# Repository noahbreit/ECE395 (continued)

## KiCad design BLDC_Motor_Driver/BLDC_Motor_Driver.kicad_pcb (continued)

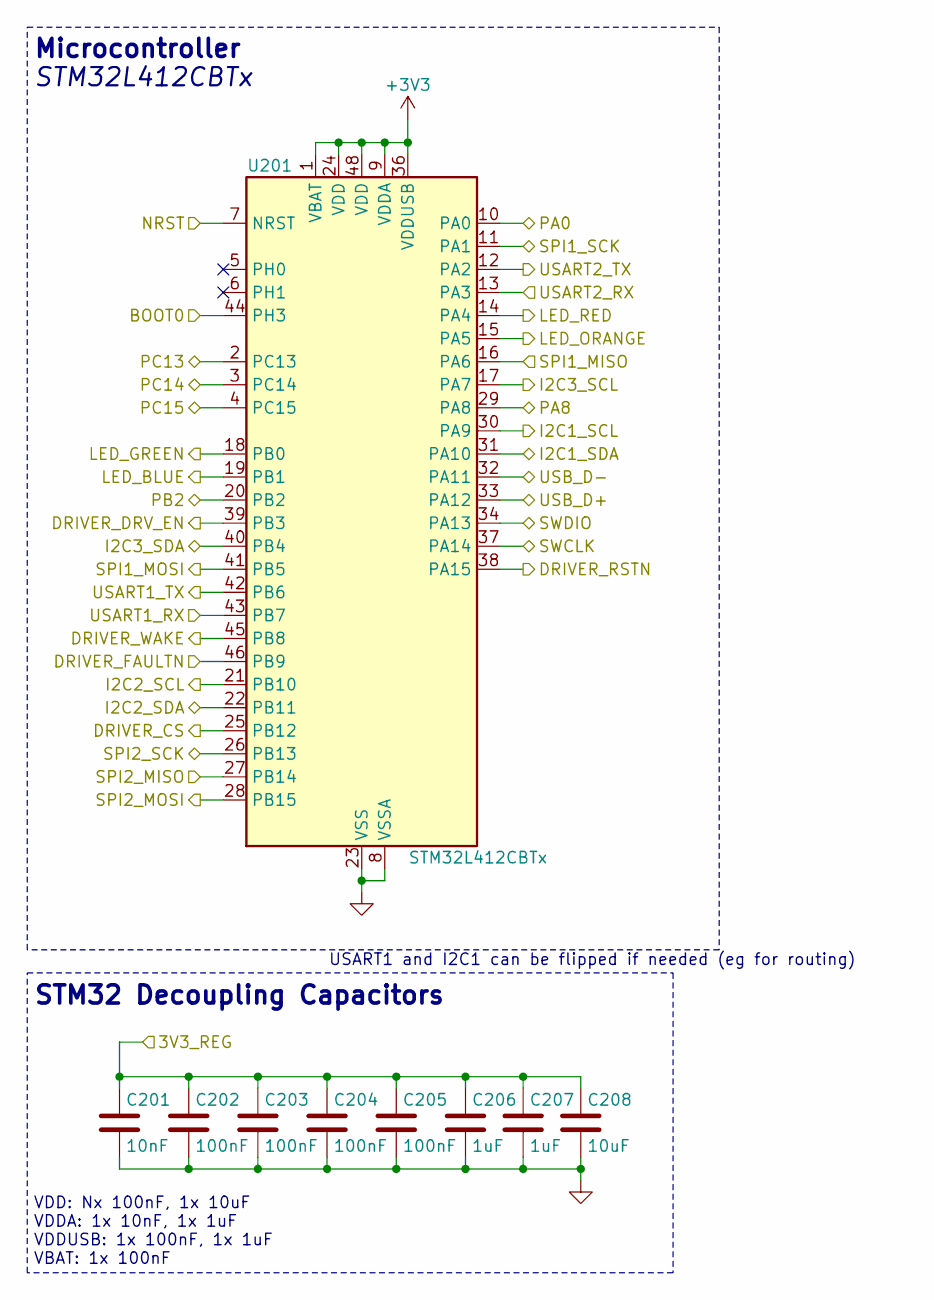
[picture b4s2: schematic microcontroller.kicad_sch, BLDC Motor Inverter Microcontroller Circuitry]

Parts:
C201: 10nF; C_0603_1608Metric
C202, C203, C204, C205: 100nF; C_0603_1608Metric
C206, C207: 1uF; C_0603_1608Metric
C208: 10uF; C_0603_1608Metric
U201: STM32L412CBTx; LQFP-48_7x7mm_P0.5mm

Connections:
+3V3: C201.1, C202.1, C203.1, C204.1, C205.1, C206.1, C207.1, C208.1, U201.1 (VBAT), U201.9 (VDDA), U201.24 (VDD), U201.36 (VDDUSB), U201.48 (VDD); also elsewhere on the board
/BOOT0: U201.44 (PH3); also elsewhere on the board
/DRIVER_CS: U201.25 (PB12); also elsewhere on the board
/DRIVER_DRV_EN: U201.39 (PB3); also elsewhere on the board
/DRIVER_FAULTN: U201.46 (PB9); also elsewhere on the board
/DRIVER_RSTN: U201.38 (PA15); also elsewhere on the board
/DRIVER_WAKE: U201.45 (PB8); also elsewhere on the board
/I2C1_SCL: U201.30 (PA9); also elsewhere on the board
/I2C1_SDA: U201.31 (PA10); also elsewhere on the board
/I2C2_SCL: U201.21 (PB10); also elsewhere on the board
/I2C2_SDA: U201.22 (PB11); also elsewhere on the board
/I2C3_SCL: U201.17 (PA7); also elsewhere on the board
/I2C3_SDA: U201.40 (PB4); also elsewhere on the board
/LED_BLUE: U201.14 (PA4); also elsewhere on the board
/LED_GREEN: U201.15 (PA5); also elsewhere on the board
/LED_ORANGE: U201.18 (PB0); also elsewhere on the board
/LED_RED: U201.19 (PB1); also elsewhere on the board
/NRST: U201.7 (NRST); also elsewhere on the board
/PA0: U201.10 (PA0); also elsewhere on the board
/PA8: U201.29 (PA8); also elsewhere on the board
/PB2: U201.20 (PB2); also elsewhere on the board
/PC13: U201.2 (PC13); also elsewhere on the board
/PC14: U201.3 (PC14); also elsewhere on the board
/PC15: U201.4 (PC15); also elsewhere on the board
/SPI1_MISO: U201.16 (PA6); also elsewhere on the board
/SPI1_MOSI: U201.41 (PB5); also elsewhere on the board
/SPI1_SCK: U201.11 (PA1); also elsewhere on the board
/SPI2_MISO: U201.27 (PB14); also elsewhere on the board
/SPI2_MOSI: U201.28 (PB15); also elsewhere on the board
/SPI2_SCK: U201.26 (PB13); also elsewhere on the board
/SWCLK: U201.34 (PA13); also elsewhere on the board
/SWDIO: U201.37 (PA14); also elsewhere on the board
/USART1_RX: U201.43 (PB7); also elsewhere on the board
/USART1_TX: U201.42 (PB6); also elsewhere on the board
/USART2_RX: U201.13 (PA3); also elsewhere on the board
/USART2_TX: U201.12 (PA2); also elsewhere on the board
/USB_D+: U201.33 (PA12); also elsewhere on the board
/USB_D-: U201.32 (PA11); also elsewhere on the board
GND: C201.2, C202.2, C203.2, C204.2, C205.2, C206.2, C207.2, C208.2, U201.8 (VSSA), U201.23 (VSS), U201.35 (VSS), U201.47 (VSS); also elsewhere on the board

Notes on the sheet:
USART1 and I2C1 can be flipped if needed (eg for routing)
VDD: Nx 100nF, 1x 10uF VDDA: 1x 10nF, 1x 1uF VDDUSB: 1x 100nF, 1x 1uF VBAT: 1x 100nF
STM32 Decoupling Capacitors
STM32L412CBTx
Microcontroller

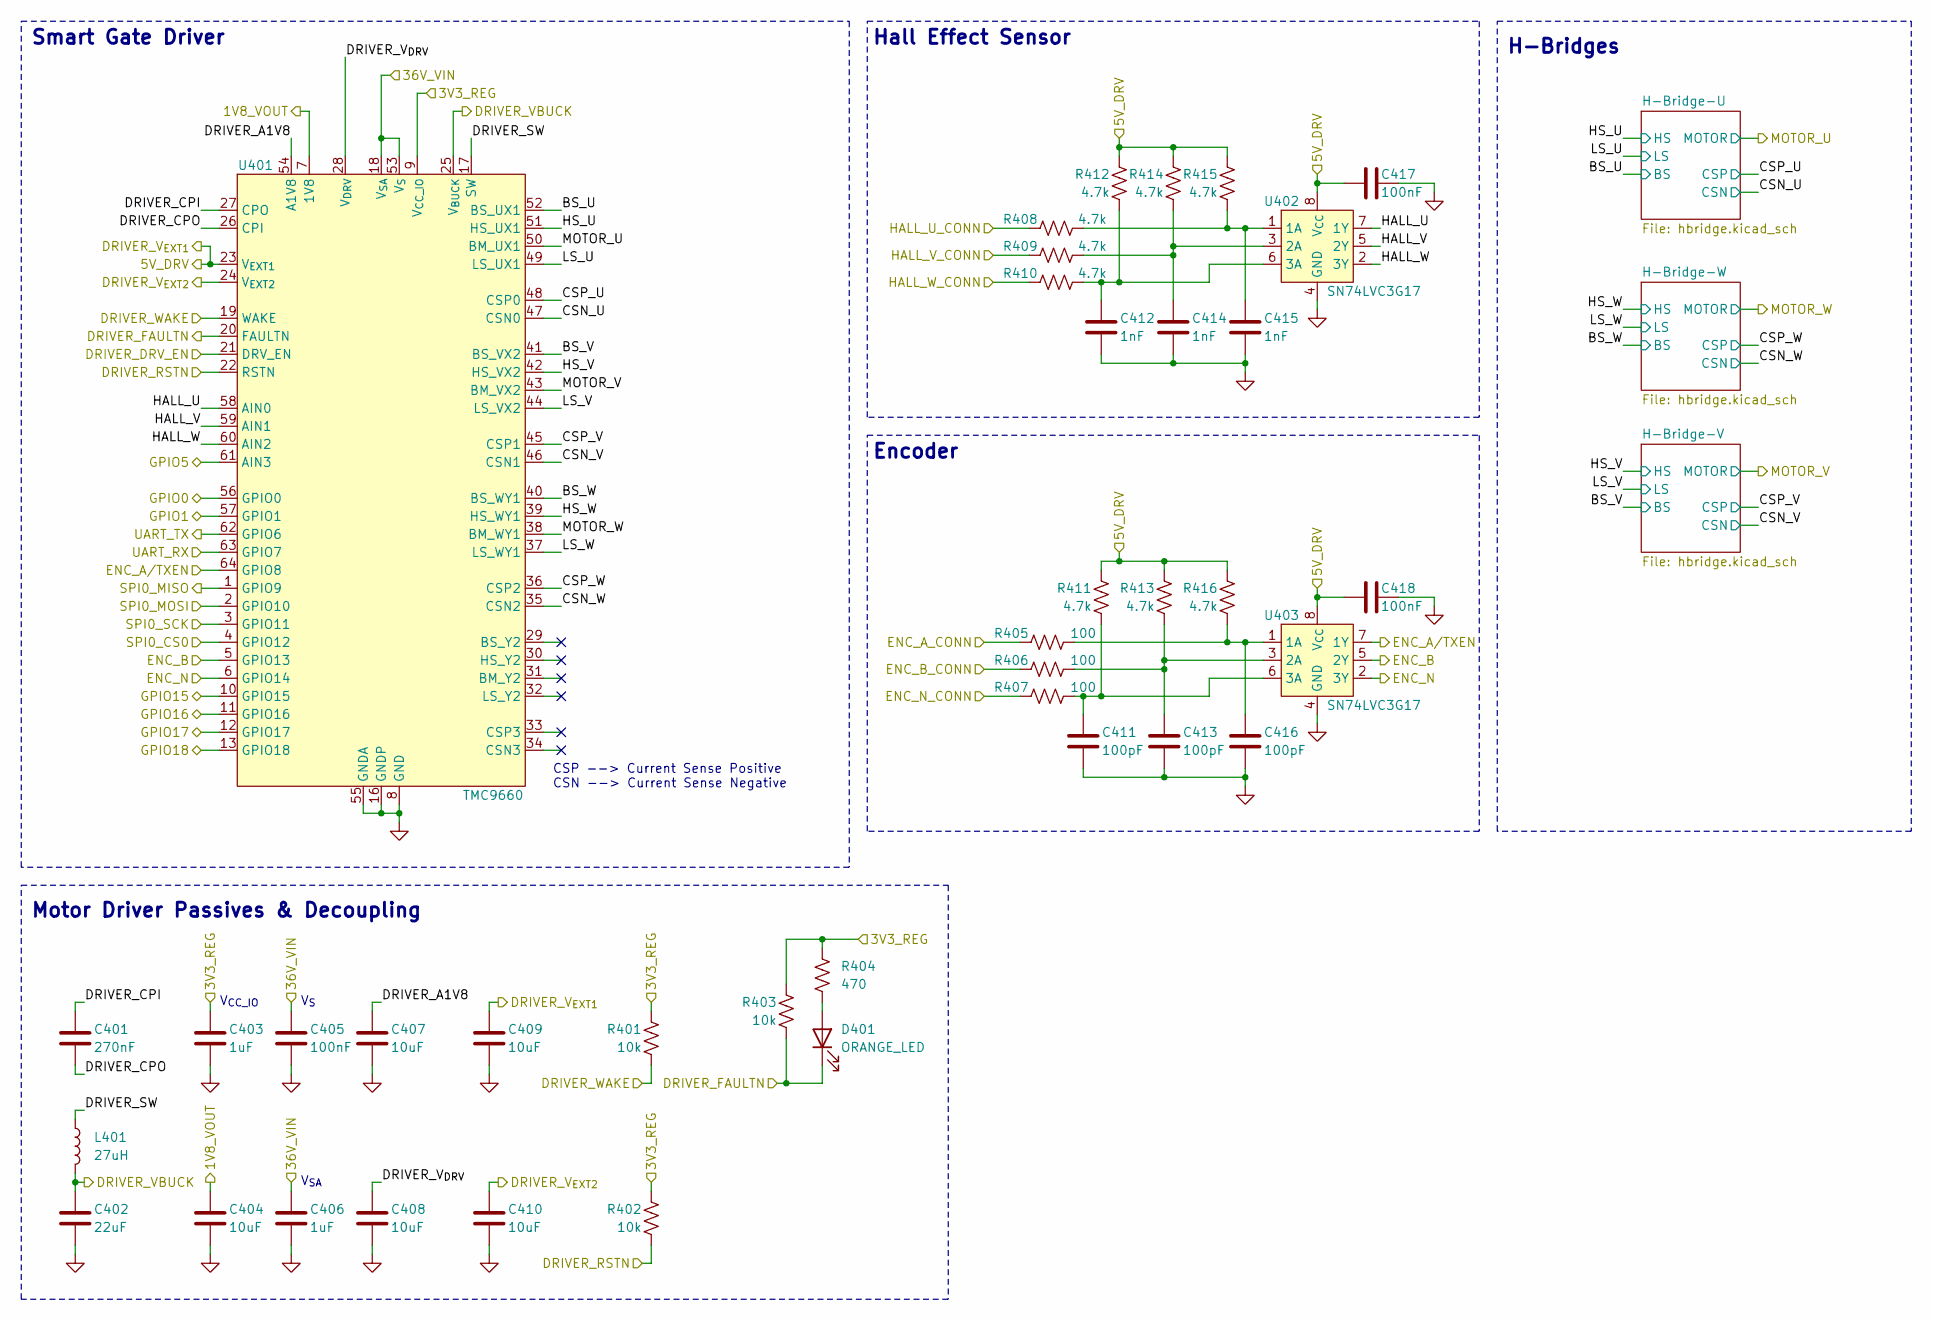
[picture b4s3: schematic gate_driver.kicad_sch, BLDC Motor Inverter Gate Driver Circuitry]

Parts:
C401: 270nF; C_0603_1608Metric
C402: 22uF; C_0805_2012Metric
C403: 1uF; C_0603_1608Metric
C404, C407: 10uF; C_0805_2012Metric
C405: 100nF; C_0805_2012Metric
C406: 1uF; C_1206_3216Metric
C408: 10uF; C_1206_3216Metric
C409, C410: 10uF; C_0603_1608Metric
C411, C413, C416: 100pF; C_0603_1608Metric
C412, C414, C415: 1nF; C_0603_1608Metric
C417, C418: 100nF; C_0603_1608Metric
D401: ORANGE_LED; LED_0603_1608Metric
L401: 27uH; L_APV_ANR6045
R401, R402, R403: 10k; R_0603_1608Metric
R404: 470; R_0603_1608Metric
R405, R406, R407: 100; R_0603_1608Metric
R408, R409, R410, R411, R412, R413, R414, R415, R416: 4.7k; R_0603_1608Metric
U401: TMC9660; QFN-64-1EP_9x9mm_P0.5mm_EP6.3x6.3mm
U402, U403: SN74LVC3G17; VSSOP-8_2.3x2mm_P0.5mm

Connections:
+1V8: C404.1, U401.7 (1V8); also elsewhere on the board
+3V3: C403.1, R401.1, R402.1, R403.1, R404.1, U401.9 (V_{CC_IO}); also elsewhere on the board
+36V: C405.1, C406.1, U401.18 (V_{SA}), U401.53 (V_{S}); also elsewhere on the board
/5V_DRV: C409.1, C417.1, C418.1, R411.1, R412.1, R413.1, R414.1, R415.1, R416.1, U401.23 (V_{EXT1}), U402.8 (V_{CC}), U403.8 (V_{CC}); also elsewhere on the board
/DRIVER_CS: U401.4 (GPIO12); also elsewhere on the board
/DRIVER_DRV_EN: U401.21 (DRV_EN); also elsewhere on the board
/DRIVER_FAULTN: D401.1 (K), R403.2, U401.20 (FAULTN); also elsewhere on the board
/DRIVER_RSTN: R402.2, U401.22 (RSTN); also elsewhere on the board
/DRIVER_V_{BUCK}: C402.1, L401.2, U401.25 (V_{BUCK}); also elsewhere on the board
/DRIVER_V_{EXT2}: C410.1, U401.24 (V_{EXT2}); also elsewhere on the board
/DRIVER_WAKE: R401.2, U401.19 (WAKE); also elsewhere on the board
/ENC_A_CONN: R405.1; also elsewhere on the board
/ENC_B_CONN: R406.1; also elsewhere on the board
/ENC_N_CONN: R407.1; also elsewhere on the board
/Gate-Driver/BS_U: U401.52 (BS_UX1); also elsewhere on the board
/Gate-Driver/BS_V: U401.41 (BS_VX2); also elsewhere on the board
/Gate-Driver/BS_W: U401.40 (BS_WY1); also elsewhere on the board
/Gate-Driver/CSN_U: U401.47 (CSN0); also elsewhere on the board
/Gate-Driver/CSN_V: U401.46 (CSN1); also elsewhere on the board
/Gate-Driver/CSN_W: U401.35 (CSN2); also elsewhere on the board
/Gate-Driver/CSP_U: U401.48 (CSP0); also elsewhere on the board
/Gate-Driver/CSP_V: U401.45 (CSP1); also elsewhere on the board
/Gate-Driver/CSP_W: U401.36 (CSP2); also elsewhere on the board
/Gate-Driver/DRIVER_A1V8: C407.1, U401.54 (A1V8)
/Gate-Driver/DRIVER_CPI: C401.1, U401.27 (CPO)
/Gate-Driver/DRIVER_CPO: C401.2, U401.26 (CPI)
/Gate-Driver/DRIVER_SW: L401.1, U401.17 (SW)
/Gate-Driver/DRIVER_V_{DRV}: C408.1, U401.28 (V_{DRV})
/Gate-Driver/ENC_A/TXEN: U401.64 (GPIO8), U403.7 (1Y); also elsewhere on the board
/Gate-Driver/ENC_B: U401.5 (GPIO13), U403.5 (2Y)
/Gate-Driver/ENC_N: U401.6 (GPIO14), U403.2 (3Y)
/Gate-Driver/GPIO0: U401.56 (GPIO0); also elsewhere on the board
/Gate-Driver/GPIO1: U401.57 (GPIO1); also elsewhere on the board
/Gate-Driver/GPIO5: U401.61 (AIN3); also elsewhere on the board
/Gate-Driver/GPIO15: U401.10 (GPIO15); also elsewhere on the board
/Gate-Driver/GPIO16: U401.11 (GPIO16); also elsewhere on the board
/Gate-Driver/GPIO17: U401.12 (GPIO17); also elsewhere on the board
/Gate-Driver/GPIO18: U401.13 (GPIO18); also elsewhere on the board
/Gate-Driver/HALL_U: U401.58 (AIN0), U402.7 (1Y)
/Gate-Driver/HALL_V: U401.59 (AIN1), U402.5 (2Y)
/Gate-Driver/HALL_W: U401.60 (AIN2), U402.2 (3Y)
/Gate-Driver/HS_U: U401.51 (HS_UX1); also elsewhere on the board
/Gate-Driver/HS_V: U401.42 (HS_VX2); also elsewhere on the board
/Gate-Driver/HS_W: U401.39 (HS_WY1); also elsewhere on the board
/Gate-Driver/LS_U: U401.49 (LS_UX1); also elsewhere on the board
/Gate-Driver/LS_V: U401.44 (LS_VX2); also elsewhere on the board
/Gate-Driver/LS_W: U401.37 (LS_WY1); also elsewhere on the board
/HALL_U_CONN: R408.1; also elsewhere on the board
/HALL_V_CONN: R409.1; also elsewhere on the board
/HALL_W_CONN: R410.1; also elsewhere on the board
/MOTOR_U: U401.50 (BM_UX1); also elsewhere on the board
/MOTOR_V: U401.43 (BM_VX2); also elsewhere on the board
/MOTOR_W: U401.38 (BM_WY1); also elsewhere on the board
/SPI2_MISO: U401.1 (GPIO9); also elsewhere on the board
/SPI2_MOSI: U401.2 (GPIO10); also elsewhere on the board
/SPI2_SCK: U401.3 (GPIO11); also elsewhere on the board
/USART1_RX: U401.62 (GPIO6); also elsewhere on the board
/USART1_TX: U401.63 (GPIO7); also elsewhere on the board
GND: C402.2, C403.2, C404.2, C405.2, C406.2, C407.2, C408.2, C409.2, C410.2, C411.2, C412.2, C413.2, C414.2, C415.2, C416.2, C417.2, C418.2, U401.8 (GND), U401.16 (GNDP), U401.55 (GNDA), U401.65 (EP), U402.4 (GND), U403.4 (GND); also elsewhere on the board
unnamed: D401.2 (A), R404.2
unnamed: C415.1, R408.2, R415.2, U402.1 (1A)
unnamed: C414.1, R409.2, R414.2, U402.3 (2A)
unnamed: C412.1, R410.2, R412.2, U402.6 (3A)
unnamed: C416.1, R405.2, R416.2, U403.1 (1A)
unnamed: C413.1, R406.2, R413.2, U403.3 (2A)
unnamed: C411.1, R407.2, R411.2, U403.6 (3A)

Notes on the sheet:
H-Bridges
V_{S}
Motor Driver Passives & Decoupling
Hall Effect Sensor
V_{CC_IO}
Encoder
Smart Gate Driver
CSP --> Current Sense Positive CSN --> Current Sense Negative
V_{SA}

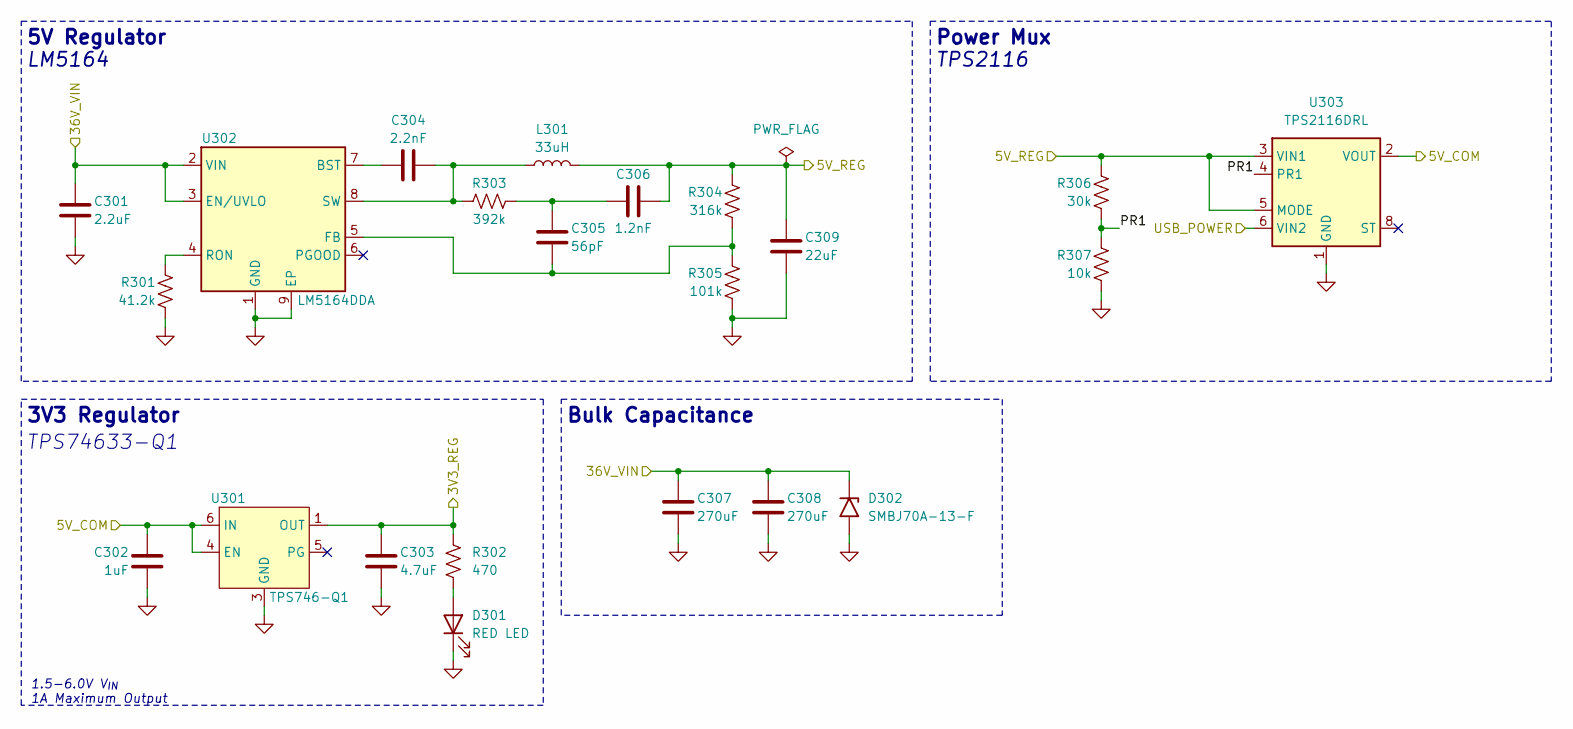
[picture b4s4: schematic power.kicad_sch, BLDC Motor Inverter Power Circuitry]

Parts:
C301: 2.2uF; C_1210_3225Metric
C302: 1uF; C_0603_1608Metric
C303: 4.7uF; C_0603_1608Metric
C304: 2.2nF; C_0805_2012Metric
C305: 56pF; C_0805_2012Metric
C306: 1.2nF; C_0603_1608Metric
C307, C308: 270uF; CP_Radial_D16.0mm_P7.50mm
C309: 22uF; C_1206_3216Metric
D301: RED LED; LED_0603_1608Metric
D302: SMBJ70A-13-F; D_SMB
L301: 33uH; L_Vishay_IHLP-3232
R301: 41.2k; R_0603_1608Metric
R302: 470; R_0603_1608Metric
R303: 392k; R_0603_1608Metric
R304: 316k; R_0603_1608Metric
R305: 101k; R_0603_1608Metric
R306: 30k; R_0603_1608Metric
R307: 10k; R_0603_1608Metric
U301: TPS746-Q1; WSON-6-1EP_2x2mm_P0.65mm_EP1x1.6mm
U302: LM5164DDA; HSOP-8-1EP_3.9x4.9mm_P1.27mm_EP2.41x3.1mm_ThermalVias
U303: TPS2116DRL; SOT-583-8

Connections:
+3V3: C303.1, R302.1, U301.1 (OUT); also elsewhere on the board
+36V: C301.1, C307.1, C308.1, D302.1 (A1), U302.2 (VIN), U302.3 (EN/UVLO); also elsewhere on the board
/5V_COM: C302.1, U301.4 (EN), U301.6 (IN), U303.2 (VOUT), U303.7 (VOUT); also elsewhere on the board
/5V_REG: C306.2, C309.1, L301.2, R304.1, R306.1, U303.3 (VIN1), U303.5 (MODE); also elsewhere on the board
/Power/PR1: R306.2, R307.1, U303.4 (PR1)
/USB_POWER: U303.6 (VIN2); also elsewhere on the board
GND: C301.2, C302.2, C303.2, C307.2, C308.2, C309.2, D301.1 (K), D302.2 (A2), R301.2, R305.2, R307.2, U301.3 (GND), U301.7 (EP), U302.1 (GND), U302.9 (EP), U303.1 (GND); also elsewhere on the board
unnamed: C305.1, C306.1, R303.2
unnamed: D301.2 (A), R302.2
unnamed: C304.1, U302.7 (BST)
unnamed: C305.2, R304.2, R305.1, U302.5 (FB)
unnamed: R301.1, U302.4 (RON)
unnamed: C304.2, L301.1, R303.1, U302.8 (SW)

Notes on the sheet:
5V Regulator
Bulk Capacitance
LM5164
Power Mux
TPS74633-Q1
TPS2116
3V3 Regulator
1.5-6.0V V_{IN} 1A Maximum Output

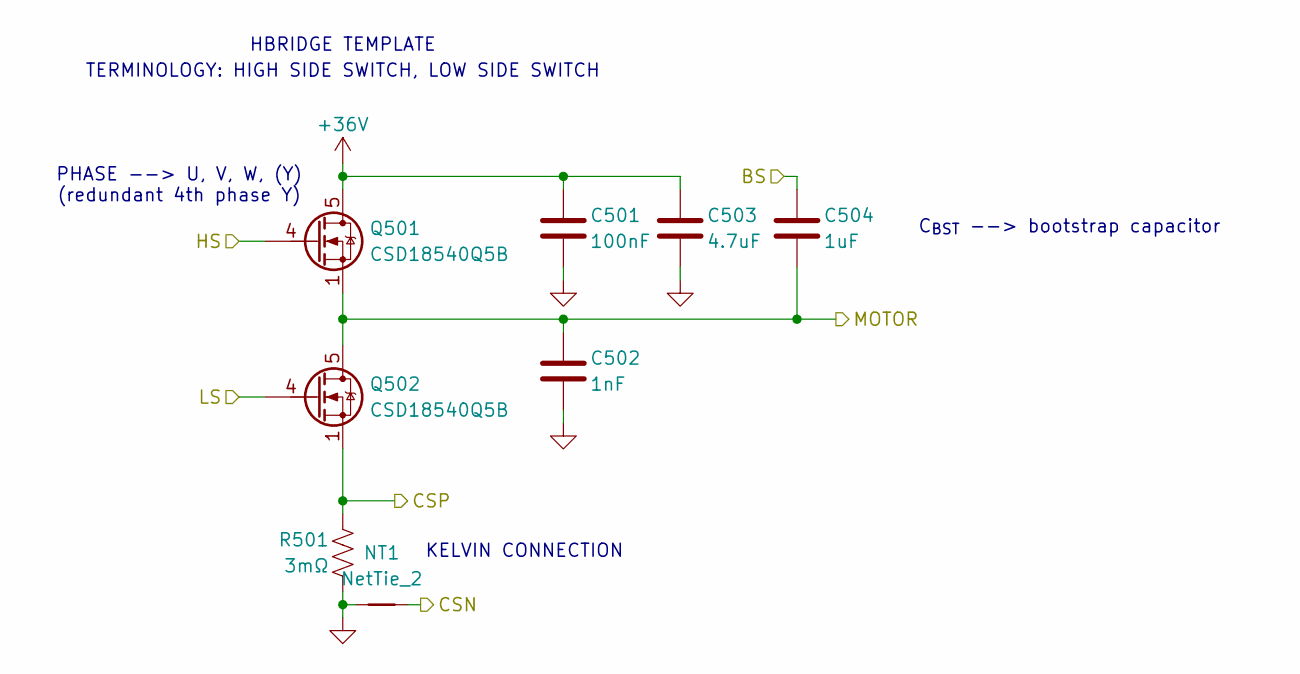
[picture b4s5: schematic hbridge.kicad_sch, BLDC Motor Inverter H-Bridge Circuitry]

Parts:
C501: 100nF; C_0805_2012Metric
C502: 1nF; C_0603_1608Metric
C503: 4.7uF; C_1210_3225Metric
C504: 1uF; C_0603_1608Metric
NT1: NetTie_2; NetTie-2_THT_Pad0.3mm
Q501, Q502: CSD18540Q5B; TDSON-8-1
R501: 3mΩ; R_2512_6332Metric_Pad1.40x3.35mm_HandSolder

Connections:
+36V: C501.1, C503.1, Q501.5 (D); also elsewhere on the board
/Gate-Driver/BS_U: C504.1; also elsewhere on the board
/Gate-Driver/CSN_U: NT1.2; also elsewhere on the board
/Gate-Driver/CSP_U: Q502.1 (S), Q502.2 (S), Q502.3 (S), R501.1; also elsewhere on the board
/Gate-Driver/HS_U: Q501.4 (G); also elsewhere on the board
/Gate-Driver/LS_U: Q502.4 (G); also elsewhere on the board
/MOTOR_U: C502.1, C504.2, Q501.1 (S), Q501.2 (S), Q501.3 (S), Q502.5 (D); also elsewhere on the board
GND: C501.2, C502.2, C503.2, NT1.1, R501.2; also elsewhere on the board

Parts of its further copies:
C601, C701: 100nF; C_0805_2012Metric
C602, C702: 1nF; C_0603_1608Metric
C603, C703: 4.7uF; C_1210_3225Metric
C604, C704: 1uF; C_0603_1608Metric
NT2, NT3: NetTie_2; NetTie-2_THT_Pad0.3mm
Q601, Q602, Q701, Q702: CSD18540Q5B; TDSON-8-1
R601, R701: 3mΩ; R_2512_6332Metric_Pad1.40x3.35mm_HandSolder

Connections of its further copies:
+36V: C601.1, C603.1, C701.1, C703.1, Q601.5 (D), Q701.5 (D); also elsewhere on the board
/Gate-Driver/BS_V: C604.1; also elsewhere on the board
/Gate-Driver/BS_W: C704.1; also elsewhere on the board
/Gate-Driver/CSN_V: NT2.2; also elsewhere on the board
/Gate-Driver/CSN_W: NT3.2; also elsewhere on the board
/Gate-Driver/CSP_V: Q602.1 (S), Q602.2 (S), Q602.3 (S), R601.1; also elsewhere on the board
/Gate-Driver/CSP_W: Q702.1 (S), Q702.2 (S), Q702.3 (S), R701.1; also elsewhere on the board
/Gate-Driver/HS_V: Q601.4 (G); also elsewhere on the board
/Gate-Driver/HS_W: Q701.4 (G); also elsewhere on the board
/Gate-Driver/LS_V: Q602.4 (G); also elsewhere on the board
/Gate-Driver/LS_W: Q702.4 (G); also elsewhere on the board
/MOTOR_V: C602.1, C604.2, Q601.1 (S), Q601.2 (S), Q601.3 (S), Q602.5 (D); also elsewhere on the board
/MOTOR_W: C702.1, C704.2, Q701.1 (S), Q701.2 (S), Q701.3 (S), Q702.5 (D); also elsewhere on the board
GND: C601.2, C602.2, C603.2, C701.2, C702.2, C703.2, NT2.1, NT3.1, R601.2, R701.2; also elsewhere on the board

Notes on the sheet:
TERMINOLOGY: HIGH SIDE SWITCH, LOW SIDE SWITCH
KELVIN CONNECTION
C_{BST} --> bootstrap capacitor
HBRIDGE TEMPLATE
PHASE --> U, V, W, (Y) (redundant 4th phase Y)

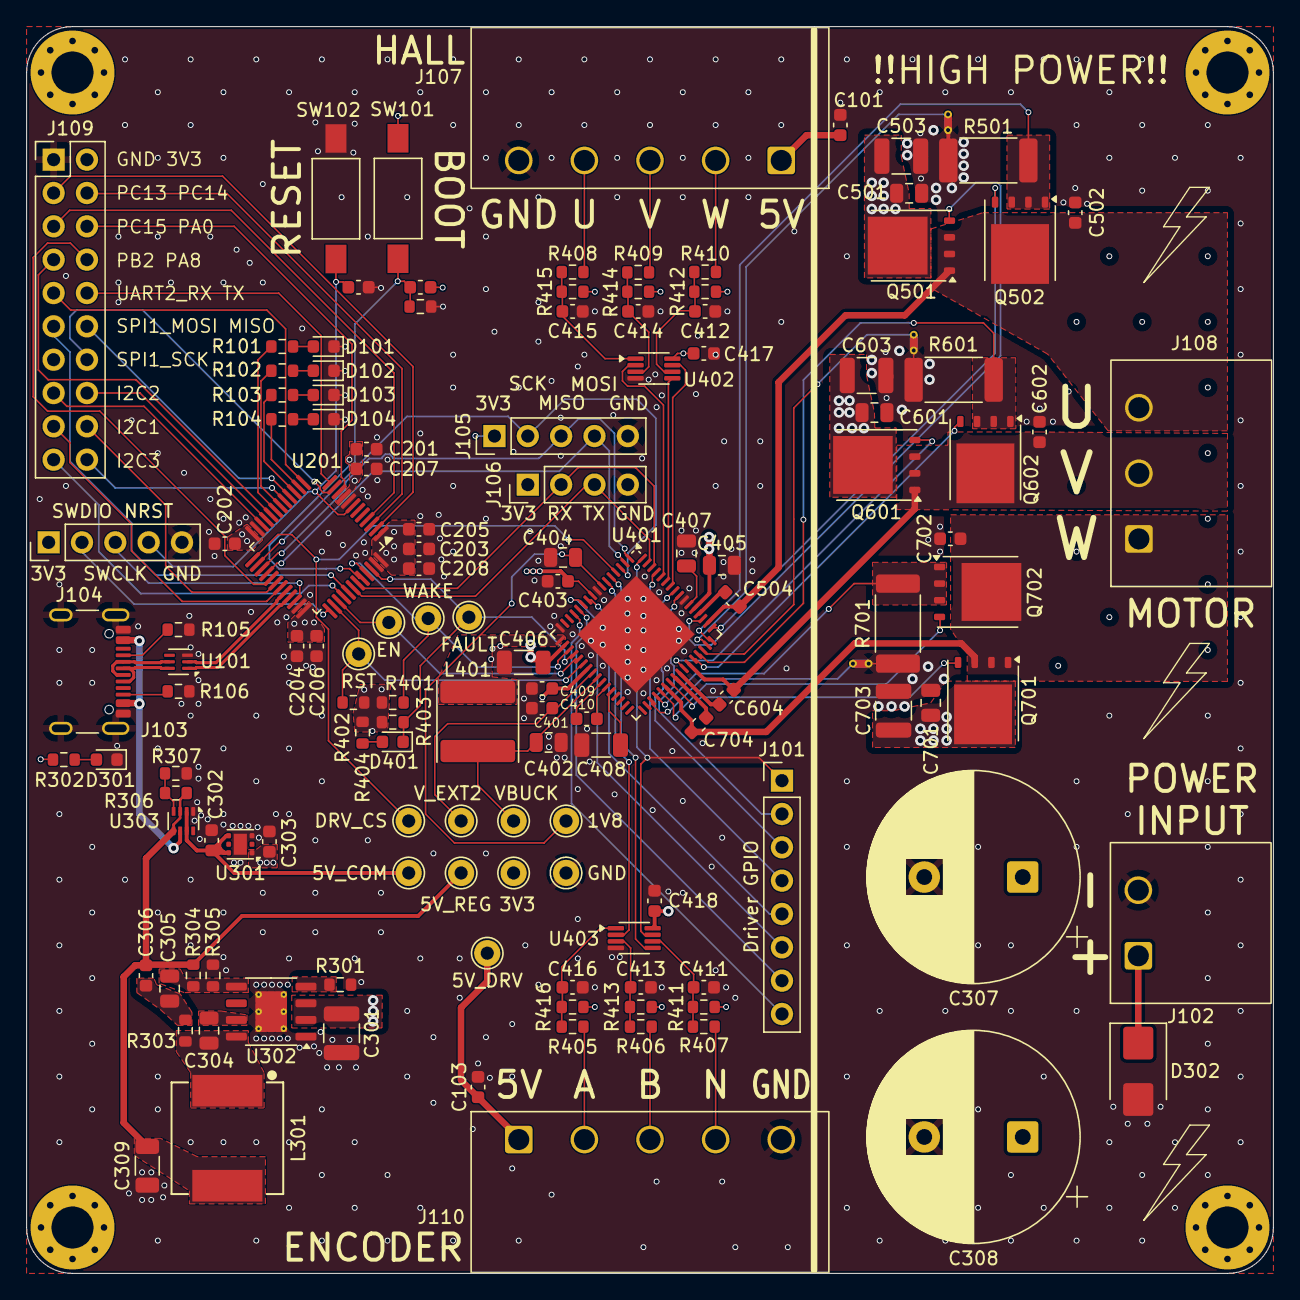
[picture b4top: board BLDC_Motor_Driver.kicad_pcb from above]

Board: 4 copper layers, 95.0 x 95.0 mm, 139 parts (0 on the bottom side), 111 nets.

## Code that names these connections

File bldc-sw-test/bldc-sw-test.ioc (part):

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Mcu.Name=STM32L412CBTx
Mcu.Package=LQFP48
Mcu.UserName=STM32L412CBTx
PA1.Signal=SPI1_SCK
PA10.Signal=I2C1_SDA
PA11.Mode=Device
PA11.Signal=USB_DM
PA12.Mode=Device
PA12.Signal=USB_DP
PA15\ (JTDI).Signal=GPIO_Output
PA2.Signal=USART2_TX
PA3.Signal=USART2_RX
PA4.Signal=GPIO_Output
PA5.Signal=GPIO_Output
PA6.Signal=SPI1_MISO
PA7.Signal=I2C3_SCL
PA9.Signal=I2C1_SCL
PB0.Signal=GPIO_Output
PB1.Signal=GPIO_Output
PB10.Signal=I2C2_SCL
PB11.Signal=I2C2_SDA
PB12.Signal=GPIO_Output
PB13.Signal=SPI2_SCK
PB14.Signal=SPI2_MISO
PB15.Signal=SPI2_MOSI
PB3\ (JTDO/TRACESWO).Signal=GPIO_Output
PB4\ (NJTRST).Signal=I2C3_SDA
PB5.Signal=SPI1_MOSI
PB6.Mode=Asynchronous
PB6.Signal=USART1_TX
PB7.Mode=Asynchronous
PB7.Signal=USART1_RX
PB8.Signal=GPIO_Output
PB9.Signal=GPIO_Input
RCC.HSE_VALUE=8000000
RCC.SYSCLKFreq_VALUE=80000000
RCC.SYSCLKSource=RCC_SYSCLKSOURCE_PLLCLK
board=custom

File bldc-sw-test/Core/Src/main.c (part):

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}

/* * Holds the TMC9660 in hardware reset and waits for a user start command.
 * Note: Uses PA15 (RSTN) and monitors PB9 (FAULTN) per schematic labels.
 */
void tmc9660_app_HoldInResetUntilReady(void) {
    uint8_t user_cmd = 0;
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    // 1. Assert Hardware Reset (Active Low)
    HAL_GPIO_WritePin(GPIOA, GPIO_PIN_15, GPIO_PIN_RESET);

    // 2. Ensure Wake is high (PB8 is DRIVER_WAKE in schematic)
    HAL_GPIO_WritePin(GPIOB, GPIO_PIN_8, GPIO_PIN_SET);

    // 3. Ensure Drive_En is low (PB3)
    HAL_GPIO_WritePin(GPIOB, GPIO_PIN_3, GPIO_PIN_RESET);

    UART_Printf("\r\n[SYSTEM] TMC9660 held in RESET to prevent brownout.\r\n");
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            UserRxBufferFS[0] = 0; // Clear for next use
        }

        // Optional: Monitor Fault pin (PB9) while waiting
        if (HAL_GPIO_ReadPin(GPIOB, GPIO_PIN_9) == GPIO_PIN_RESET) {
            // Add warning if driver indicates a hardware fault during standby
        }
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 */
void tmc9660_app_ReportConditionAndHalt(void) {
    // 1. Assert Safe State (Active Off)
    // DRIVER_DRV_EN (PB3): Setting LOW to disable the gate driver bridge
    HAL_GPIO_WritePin(GPIOB, GPIO_PIN_3, GPIO_PIN_RESET);

    // DRIVER_RSTN (PA15): Pulling LOW to hold the TMC9660 in Hardware Reset
    HAL_GPIO_WritePin(GPIOA, GPIO_PIN_15, GPIO_PIN_RESET);

    // 2. Read Fault Condition
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}

void tmc9660_app_EnableDrive(void) {
	// Set Drive_En is HIGH (PB3)
	HAL_GPIO_WritePin(GPIOB, GPIO_PIN_3, GPIO_PIN_SET);
}

void tmc9660_app_DisableDrive(void) {
	// Set Drive_En is LOW (PB3)
	HAL_GPIO_WritePin(GPIOB, GPIO_PIN_3, GPIO_PIN_RESET);
}

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    }

    // 3. INTERFACE CONFIG
    // UART Enable (Disable=0), SPI Slave Disable(1), TX=GPIO6(0), RX=GPIO7(0), Baud=auto16(7), SCK=GPIO11(1)
    blStatus = tmc9660_bl_sendCommand(tmc9660_id, TMC9660_BLCMD_SET_ADDRESS, CONFIG_BOOT_03_BOOT_INTERFACE, &rVal);
    if (blStatus != TMC9660_BLSTATUS_OK) {
  	  ERR_Handler(__LINE__);
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    }
    reg = field_update16(reg, CONFIG_BOOT_03_INTERFACE_BL_DISABLE_UART_FIELD, 0); // Default: 0
    reg = field_update16(reg, CONFIG_BOOT_03_INTERFACE_BL_DISABLE_SPI_FIELD, 1);	// Default: 0
    reg = field_update16(reg, CONFIG_BOOT_03_INTERFACE_BL_UART_TX_FIELD, 0);		/* 0: GPIO6 <--
  																				 * 1: GPIO0
  																				 */
    reg = field_update16(reg, CONFIG_BOOT_03_INTERFACE_BL_UART_RX_FIELD, 0);		/* 0: GPIO7	<--
  																				 * 1: GPIO0
  																				 */
    reg = field_update16(reg, CONFIG_BOOT_03_INTERFACE_BL_UART_BAUDRATE_FIELD, 7);/* 0: 9600
  																				 * 1: 19200
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  																				 * 6: auto8
  																				 * 7: auto16 <--
  																				 */
    reg = field_update16(reg, CONFIG_BOOT_03_INTERFACE_BL_SPI0_SCK_FIELD, 1);		/* 0: GPIO6
  																				 * 1: GPIO11 <--
  																				 * Note: This is bit is only required for
  																				 * the SPI bootloader communication if it
  																				 * uses SPI0 (BL_SPI_SELECT=0)
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    }

    // 4. SPI FLASH
    // Enable=true, CS=GPIO12, Freq=10MHz(3 @ 40MHz Sys)
    blStatus = tmc9660_bl_sendCommand(tmc9660_id, TMC9660_BLCMD_SET_ADDRESS, CONFIG_BOOT_05_FLASH, &rVal);
    if (blStatus != TMC9660_BLSTATUS_OK) {
  	  ERR_Handler(__LINE__);
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    }
    reg = field_update16(reg, CONFIG_BOOT_10_APP_CONFIG_0_HALL_ENABLE_FIELD, 1);  // Default: 0
    reg = field_update16(reg, CONFIG_BOOT_10_APP_CONFIG_0_HALL_UX_FIELD, 0);		/* 0: GPIO2	<--
  																				 * 1: GPIO7
  																				 * 2: GPIO9
  																				 * 3: RESERVED
  																				 */
    reg = field_update16(reg, CONFIG_BOOT_10_APP_CONFIG_0_HALL_V_FIELD, 0);		/* 0: GPIO3	<--
  																				 * 1: GPIO15
  																				 * 2: RESERVED
  																				 * 3: RESERVED
  																				 */
    reg = field_update16(reg, CONFIG_BOOT_10_APP_CONFIG_0_HALL_WY_FIELD, 0);		/* 0: GPIO4	<--
  																				 * 1: GPIO8
  																				 * 2: GPIO10
  																				 * 3: RESERVED
  																				 */
    blStatus = tmc9660_bl_sendCommand(tmc9660_id, TMC9660_BLCMD_SET_ADDRESS, CONFIG_BOOT_10_APP_CONFIG_0, &rVal);
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    }

    // 8. GPIO INIT (GPIO 5, 17, 18)
    // GPIO17/18: Input, Pulldown. GPIO5: Analog.
    blStatus = tmc9660_bl_sendCommand(tmc9660_id, TMC9660_BLCMD_SET_ADDRESS, CONFIG_BOOT_0B_GPIO_16_18_INIT, &rVal);
    if (blStatus != TMC9660_BLSTATUS_OK) {
  	  ERR_Handler(__LINE__);
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//    tmc9660_param_setParameter(tmc9660_id, TMC9660_PARAM_COMMUTATION_MODE, 1); // Low-side ON
    HAL_Delay(50);

    // 14. ENABLE HARDWARE DRIVE (PB3)
//    tmc9660_app_EnableDrive();

    // 15. START FOC HALL CONTROL
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  HAL_GPIO_WritePin(GPIOB, GPIO_PIN_0|GPIO_PIN_1|GPIO_PIN_12|GPIO_PIN_3
                          |GPIO_PIN_8, GPIO_PIN_RESET);

  /*Configure GPIO pins : PA1 PA6 */
  GPIO_InitStruct.Pin = GPIO_PIN_1|GPIO_PIN_6;
  GPIO_InitStruct.Mode = GPIO_MODE_AF_PP;
  GPIO_InitStruct.Pull = GPIO_NOPULL;
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  GPIO_InitStruct.Alternate = GPIO_AF5_SPI1;
  HAL_GPIO_Init(GPIOA, &GPIO_InitStruct);

  /*Configure GPIO pins : PA2 PA3 */
  GPIO_InitStruct.Pin = GPIO_PIN_2|GPIO_PIN_3;
  GPIO_InitStruct.Mode = GPIO_MODE_AF_PP;
  GPIO_InitStruct.Pull = GPIO_NOPULL;
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  GPIO_InitStruct.Alternate = GPIO_AF7_USART2;
  HAL_GPIO_Init(GPIOA, &GPIO_InitStruct);

  /*Configure GPIO pins : PA4 PA5 PA15 */
  GPIO_InitStruct.Pin = GPIO_PIN_4|GPIO_PIN_5|GPIO_PIN_15;
  GPIO_InitStruct.Mode = GPIO_MODE_OUTPUT_PP;
  GPIO_InitStruct.Pull = GPIO_NOPULL;
  GPIO_InitStruct.Speed = GPIO_SPEED_FREQ_LOW;
  HAL_GPIO_Init(GPIOA, &GPIO_InitStruct);

  /*Configure GPIO pin : PA7 */
  GPIO_InitStruct.Pin = GPIO_PIN_7;
  GPIO_InitStruct.Mode = GPIO_MODE_AF_OD;
  GPIO_InitStruct.Pull = GPIO_NOPULL;
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  GPIO_InitStruct.Alternate = GPIO_AF4_I2C3;
  HAL_GPIO_Init(GPIOA, &GPIO_InitStruct);

  /*Configure GPIO pins : PB0 PB1 PB12 PB3
                           PB8 */
  GPIO_InitStruct.Pin = GPIO_PIN_0|GPIO_PIN_1|GPIO_PIN_12|GPIO_PIN_3
                          |GPIO_PIN_8;
  GPIO_InitStruct.Mode = GPIO_MODE_OUTPUT_PP;
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  GPIO_InitStruct.Speed = GPIO_SPEED_FREQ_LOW;
  HAL_GPIO_Init(GPIOB, &GPIO_InitStruct);

  /*Configure GPIO pins : PB10 PB11 */
  GPIO_InitStruct.Pin = GPIO_PIN_10|GPIO_PIN_11;
  GPIO_InitStruct.Mode = GPIO_MODE_AF_OD;
  GPIO_InitStruct.Pull = GPIO_NOPULL;
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  GPIO_InitStruct.Alternate = GPIO_AF4_I2C2;
  HAL_GPIO_Init(GPIOB, &GPIO_InitStruct);

  /*Configure GPIO pins : PB13 PB14 PB15 */
  GPIO_InitStruct.Pin = GPIO_PIN_13|GPIO_PIN_14|GPIO_PIN_15;
  GPIO_InitStruct.Mode = GPIO_MODE_AF_PP;
  GPIO_InitStruct.Pull = GPIO_NOPULL;
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  GPIO_InitStruct.Alternate = GPIO_AF5_SPI2;
  HAL_GPIO_Init(GPIOB, &GPIO_InitStruct);

  /*Configure GPIO pins : PA9 PA10 */
  GPIO_InitStruct.Pin = GPIO_PIN_9|GPIO_PIN_10;
  GPIO_InitStruct.Mode = GPIO_MODE_AF_OD;
  GPIO_InitStruct.Pull = GPIO_NOPULL;
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  GPIO_InitStruct.Alternate = GPIO_AF4_I2C1;
  HAL_GPIO_Init(GPIOA, &GPIO_InitStruct);

  /*Configure GPIO pin : PB4 */
  GPIO_InitStruct.Pin = GPIO_PIN_4;
  GPIO_InitStruct.Mode = GPIO_MODE_AF_OD;
  GPIO_InitStruct.Pull = GPIO_NOPULL;
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  GPIO_InitStruct.Alternate = GPIO_AF4_I2C3;
  HAL_GPIO_Init(GPIOB, &GPIO_InitStruct);

  /*Configure GPIO pin : PB5 */
  GPIO_InitStruct.Pin = GPIO_PIN_5;
  GPIO_InitStruct.Mode = GPIO_MODE_AF_PP;
  GPIO_InitStruct.Pull = GPIO_NOPULL;
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  GPIO_InitStruct.Alternate = GPIO_AF5_SPI1;
  HAL_GPIO_Init(GPIOB, &GPIO_InitStruct);

  /*Configure GPIO pin : PB9 */
  GPIO_InitStruct.Pin = GPIO_PIN_9;
  GPIO_InitStruct.Mode = GPIO_MODE_INPUT;
  GPIO_InitStruct.Pull = GPIO_NOPULL;
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
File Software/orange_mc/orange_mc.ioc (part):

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Mcu.Name=STM32L476R(C-E-G)Tx
Mcu.Package=LQFP64
Mcu.UserName=STM32L476RGTx
PA13\ (JTMS-SWDIO).GPIOParameters=GPIO_Label
PA13\ (JTMS-SWDIO).GPIO_Label=TMS
PA13\ (JTMS-SWDIO).Mode=Serial_Wire
PA13\ (JTMS-SWDIO).Signal=SYS_JTMS-SWDIO
PA14\ (JTCK-SWCLK).GPIOParameters=GPIO_Label
PA14\ (JTCK-SWCLK).GPIO_Label=TCK
PA14\ (JTCK-SWCLK).Mode=Serial_Wire
PA14\ (JTCK-SWCLK).Signal=SYS_JTCK-SWCLK
PA2.GPIOParameters=GPIO_Speed,GPIO_PuPd,GPIO_Label,GPIO_Mode
PA2.GPIO_Label=USART_TX
PA2.GPIO_Mode=GPIO_MODE_AF_PP
PA2.GPIO_PuPd=GPIO_NOPULL
PA2.GPIO_Speed=GPIO_SPEED_FREQ_VERY_HIGH
PA2.Mode=Asynchronous
PA2.Signal=USART2_TX
PA3.GPIOParameters=GPIO_Speed,GPIO_PuPd,GPIO_Label,GPIO_Mode
PA3.GPIO_Label=USART_RX
PA3.GPIO_Mode=GPIO_MODE_AF_PP
PA3.GPIO_PuPd=GPIO_NOPULL
PA3.GPIO_Speed=GPIO_SPEED_FREQ_VERY_HIGH
PA3.Mode=Asynchronous
PA3.Signal=USART2_RX
PA5.GPIOParameters=GPIO_Speed,GPIO_PuPd,GPIO_Label,GPIO_ModeDefaultOutputPP
PA5.GPIO_Label=LD2 [green Led]
PA5.GPIO_ModeDefaultOutputPP=GPIO_MODE_OUTPUT_PP
PA5.GPIO_PuPd=GPIO_NOPULL
PA5.GPIO_Speed=GPIO_SPEED_FREQ_LOW
PA5.Signal=GPIO_Output
PB3\ (JTDO-TRACESWO).GPIOParameters=GPIO_Label
PB3\ (JTDO-TRACESWO).GPIO_Label=SWO
PB3\ (JTDO-TRACESWO).Signal=SYS_JTDO-SWO
PC13.GPIOParameters=GPIO_PuPd,GPIO_Label,GPIO_ModeDefaultEXTI
PC13.GPIO_Label=B1 [Blue PushButton]
PC13.GPIO_ModeDefaultEXTI=GPIO_MODE_IT_FALLING
PC13.GPIO_PuPd=GPIO_NOPULL
PC13.Signal=GPXTI13
PC14-OSC32_IN\ (PC14).Mode=LSE-External-Oscillator
PC14-OSC32_IN\ (PC14).Signal=RCC_OSC32_IN
PC15-OSC32_OUT\ (PC15).Mode=LSE-External-Oscillator
PC15-OSC32_OUT\ (PC15).Signal=RCC_OSC32_OUT
PH0-OSC_IN\ (PH0).Signal=RCC_OSC_IN
PH1-OSC_OUT\ (PH1).Signal=RCC_OSC_OUT
RCC.HSE_VALUE=8000000
RCC.SYSCLKFreq_VALUE=80000000
RCC.SYSCLKSource=RCC_SYSCLKSOURCE_PLLCLK
board=NUCLEO-L476RG
boardIOC=true

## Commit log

2025-06-14 used stm32cubemx tool to auto-generate stm32l4 firmware
2026-01-27 9660 bringup. TODO resolve HALL interface to 9660 GPIOs
2026-01-27 added microcontroller
2026-01-28 tmc9660 libraries
2026-02-03 added block diagram
2026-02-03 switched out tmc9660 symbol
2026-02-04 reorganized schematic, added some passive footprints & values
2026-02-10 started hall effect and power circuitry
2026-02-10 finished power circuitry
2026-02-11 updated README to include Start Up procedure for ADI GUI
2026-02-13 hall effect done, adding testpoints/connectors
2026-02-17 new GateDriver subsheet. reorg connectors to root sheet
2026-02-20 added breakout connector and reformatted some things
2026-02-25 schematics more or less done
2026-02-25 wired driver rst/status ios to mcu, layout setup
2026-03-01 move elements to logical regions
2026-03-01 aligned MCU and USB components
2026-03-01 complete top-layer routing for MCU, G_DRV, USB_PWR, HALL areas
2026-03-01 used external tool to duplicate half-bridge layouts. updated gitignore. redoing gate driver layout with high-side mosfet bootstrap caps
2026-03-01 Finished sub-hierarchy layouts
2026-03-02 removed unnecessary Y phase. finished Motor Conn Layout
2026-03-02 changed rst/en pullups to 3V3, rerouted 5V regulator
2026-03-03 board outline, most component placements, routed driver and some other stuff
2026-03-03 most power routing done
2026-03-05 finished Gate Driver layout. remaining: MCU
2026-03-05 finsihed first draft. DRC errors remaining
2026-03-05 clean layout done. signoff required
2026-03-05 resolved all but DRC warning
2026-03-05 fixed drc issues, added gnd vias
2026-03-06 silkscreen improvements and minor cleanup
2026-03-06 more final tweaks
2026-03-09 adding generated BOM
2026-03-18 begin breakout board to control high-torque Servo (for steering RC car)
2026-03-18 finalized schematic. footprints in progress
2026-03-20 replaced Micro with 555 Timer for PWM generation. completed most of layout
2026-03-21 Finalized layout and silkscreen
2026-03-24 quick improvement to +36 pour clearance
2026-03-24 fixed deprecaited VOUT comments
2026-03-24 simplify 555 timer circuit. update green_led switch to low-side switching
2026-03-24 completed layout rework for two 555 timers
2026-03-24 more comments on POT in 555 timer circuit and timing calculations
2026-03-24 servo board final cleanup
2026-03-24 servo breakout gerbers
2026-03-27 led + usb test code
2026-03-28 First draft of project firmware
2026-04-01 Workinggit add TMC_Bringup STM32 Nucleo Host able to Boot TMC9660 EVKIT over serial UART
2026-04-02 Added Goto_Bootmode() to override device mode on program start
2026-04-02 Success. Generating PWMs with setupQBL5704BLDCTest()
2026-04-21 new branch for tmc onboard testing. removed motor control test during boot
2026-04-21 radio stuff
2026-04-21 test project with correct MCU
2026-04-22 minor adjustments for debugging
2026-04-24 update gitignore for binaries
2026-04-24 Board boots with multiple General Errors, preventing PWM generation
